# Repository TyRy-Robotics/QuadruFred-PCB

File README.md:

# QuadruFred-PCB
A personal project Quadruped AKA QuadruFred. I have been working on for a while. I have decided to make a gen 2 and upgrade it in every way such as using custom PCB, using accelerometer for stabilization and overall a many mechanical changes to make it an overall smoother quadruped.

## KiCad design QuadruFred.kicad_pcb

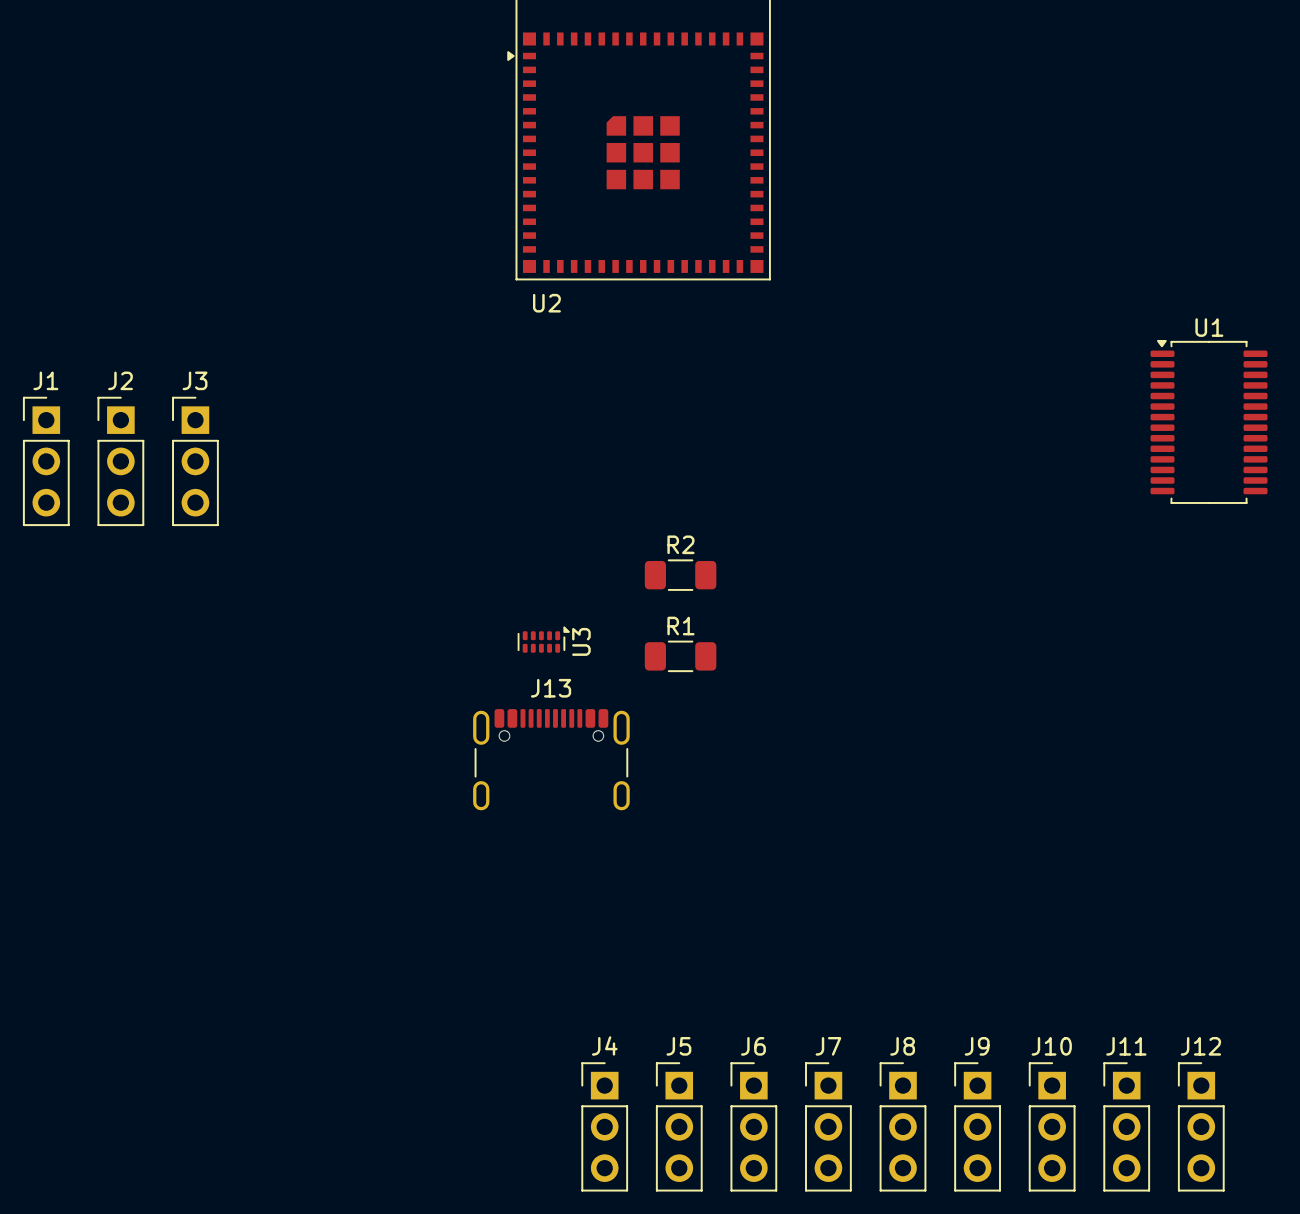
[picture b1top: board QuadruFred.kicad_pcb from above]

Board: 4 copper layers, 18 parts (0 on the bottom side), 10 nets, no tracks yet.

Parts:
J1: Servo1; PinHeader_1x03_P2.54mm_Vertical
J2: Servo2; PinHeader_1x03_P2.54mm_Vertical
J3: Servo3; PinHeader_1x03_P2.54mm_Vertical
J4: Servo4; PinHeader_1x03_P2.54mm_Vertical
J5: Servo5; PinHeader_1x03_P2.54mm_Vertical
J6: Servo6; PinHeader_1x03_P2.54mm_Vertical
J7: Servo7; PinHeader_1x03_P2.54mm_Vertical
J8: Servo8; PinHeader_1x03_P2.54mm_Vertical
J9: Servo9; PinHeader_1x03_P2.54mm_Vertical
J10: Servo10; PinHeader_1x03_P2.54mm_Vertical
J11: Servo11; PinHeader_1x03_P2.54mm_Vertical
J12: Servo12; PinHeader_1x03_P2.54mm_Vertical
J13: USB_C_Receptacle_USB2.0_16P; USB_C_Receptacle_GCT_USB4105-xx-A_16P_TopMnt_Horizontal
R1, R2: 5.1 kΩ; R_1206_3216Metric_Pad1.30x1.75mm_HandSolder
U1: PCA9685PW; TSSOP-28_4.4x9.7mm_P0.65mm
U2: ESP32-S3-MINI-1; ESP32-S2-MINI-1
U3: TPD4EUSB30; USON-10_2.5x1.0mm_P0.5mm

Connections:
+3V3: J1.2, J2.2, J3.2, J4.2, J5.2, J6.2, J7.2, J8.2, J9.2, J10.2, J11.2, J12.2, U1.28 (VDD), U2.3 (3V3)
/DP1: J13.A6 (D+), U3.2 (D1-), U3.9 (NC)
/DP2: J13.A7 (D-), U3.1 (D1+), U3.10 (NC)
/USB 5V: J13.A4 (VBUS), J13.A9 (VBUS), J13.B4 (VBUS), J13.B9 (VBUS), U3.4 (D2+), U3.7 (NC)
GND: J1.3, J2.3, J3.3, J4.3, J5.3, J6.3, J7.3, J8.3, J9.3, J10.3, J11.3, J12.3, J13.A1 (GND), J13.A12 (GND), J13.B1 (GND), J13.B12 (GND), J13.S1 (SHIELD), R1.2, R2.2, U1.14 (VSS), U2.1 (GND), U2.2 (GND), U2.42 (GND), U2.43 (GND), U2.46 (GND), U2.47 (GND), U2.48 (GND), U2.49 (GND), U2.50 (GND), U2.51 (GND), U2.52 (GND), U2.53 (GND), U2.54 (GND), U2.55 (GND), U2.56 (GND), U2.57 (GND), U2.58 (GND), U2.59 (GND), U2.60 (GND), U2.61 (GND), U2.62 (GND), U2.63 (GND), U2.64 (GND), U2.65 (GND), U3.3 (GND), U3.8 (GND)
unnamed: J10.1, U1.8 (LED2)
unnamed: J11.1, U1.7 (LED1)
unnamed: J12.1, U1.6 (LED0)
unnamed: J13.A5 (CC1), R2.1
unnamed: J13.B5 (CC2), R1.1

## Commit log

2025-06-05 Create kicad Doc
2025-06-05 Add basic leg boards and eps 32. No in depth wiring done.
2025-06-06 Finish USB circut and work finish ESP32 main connections
